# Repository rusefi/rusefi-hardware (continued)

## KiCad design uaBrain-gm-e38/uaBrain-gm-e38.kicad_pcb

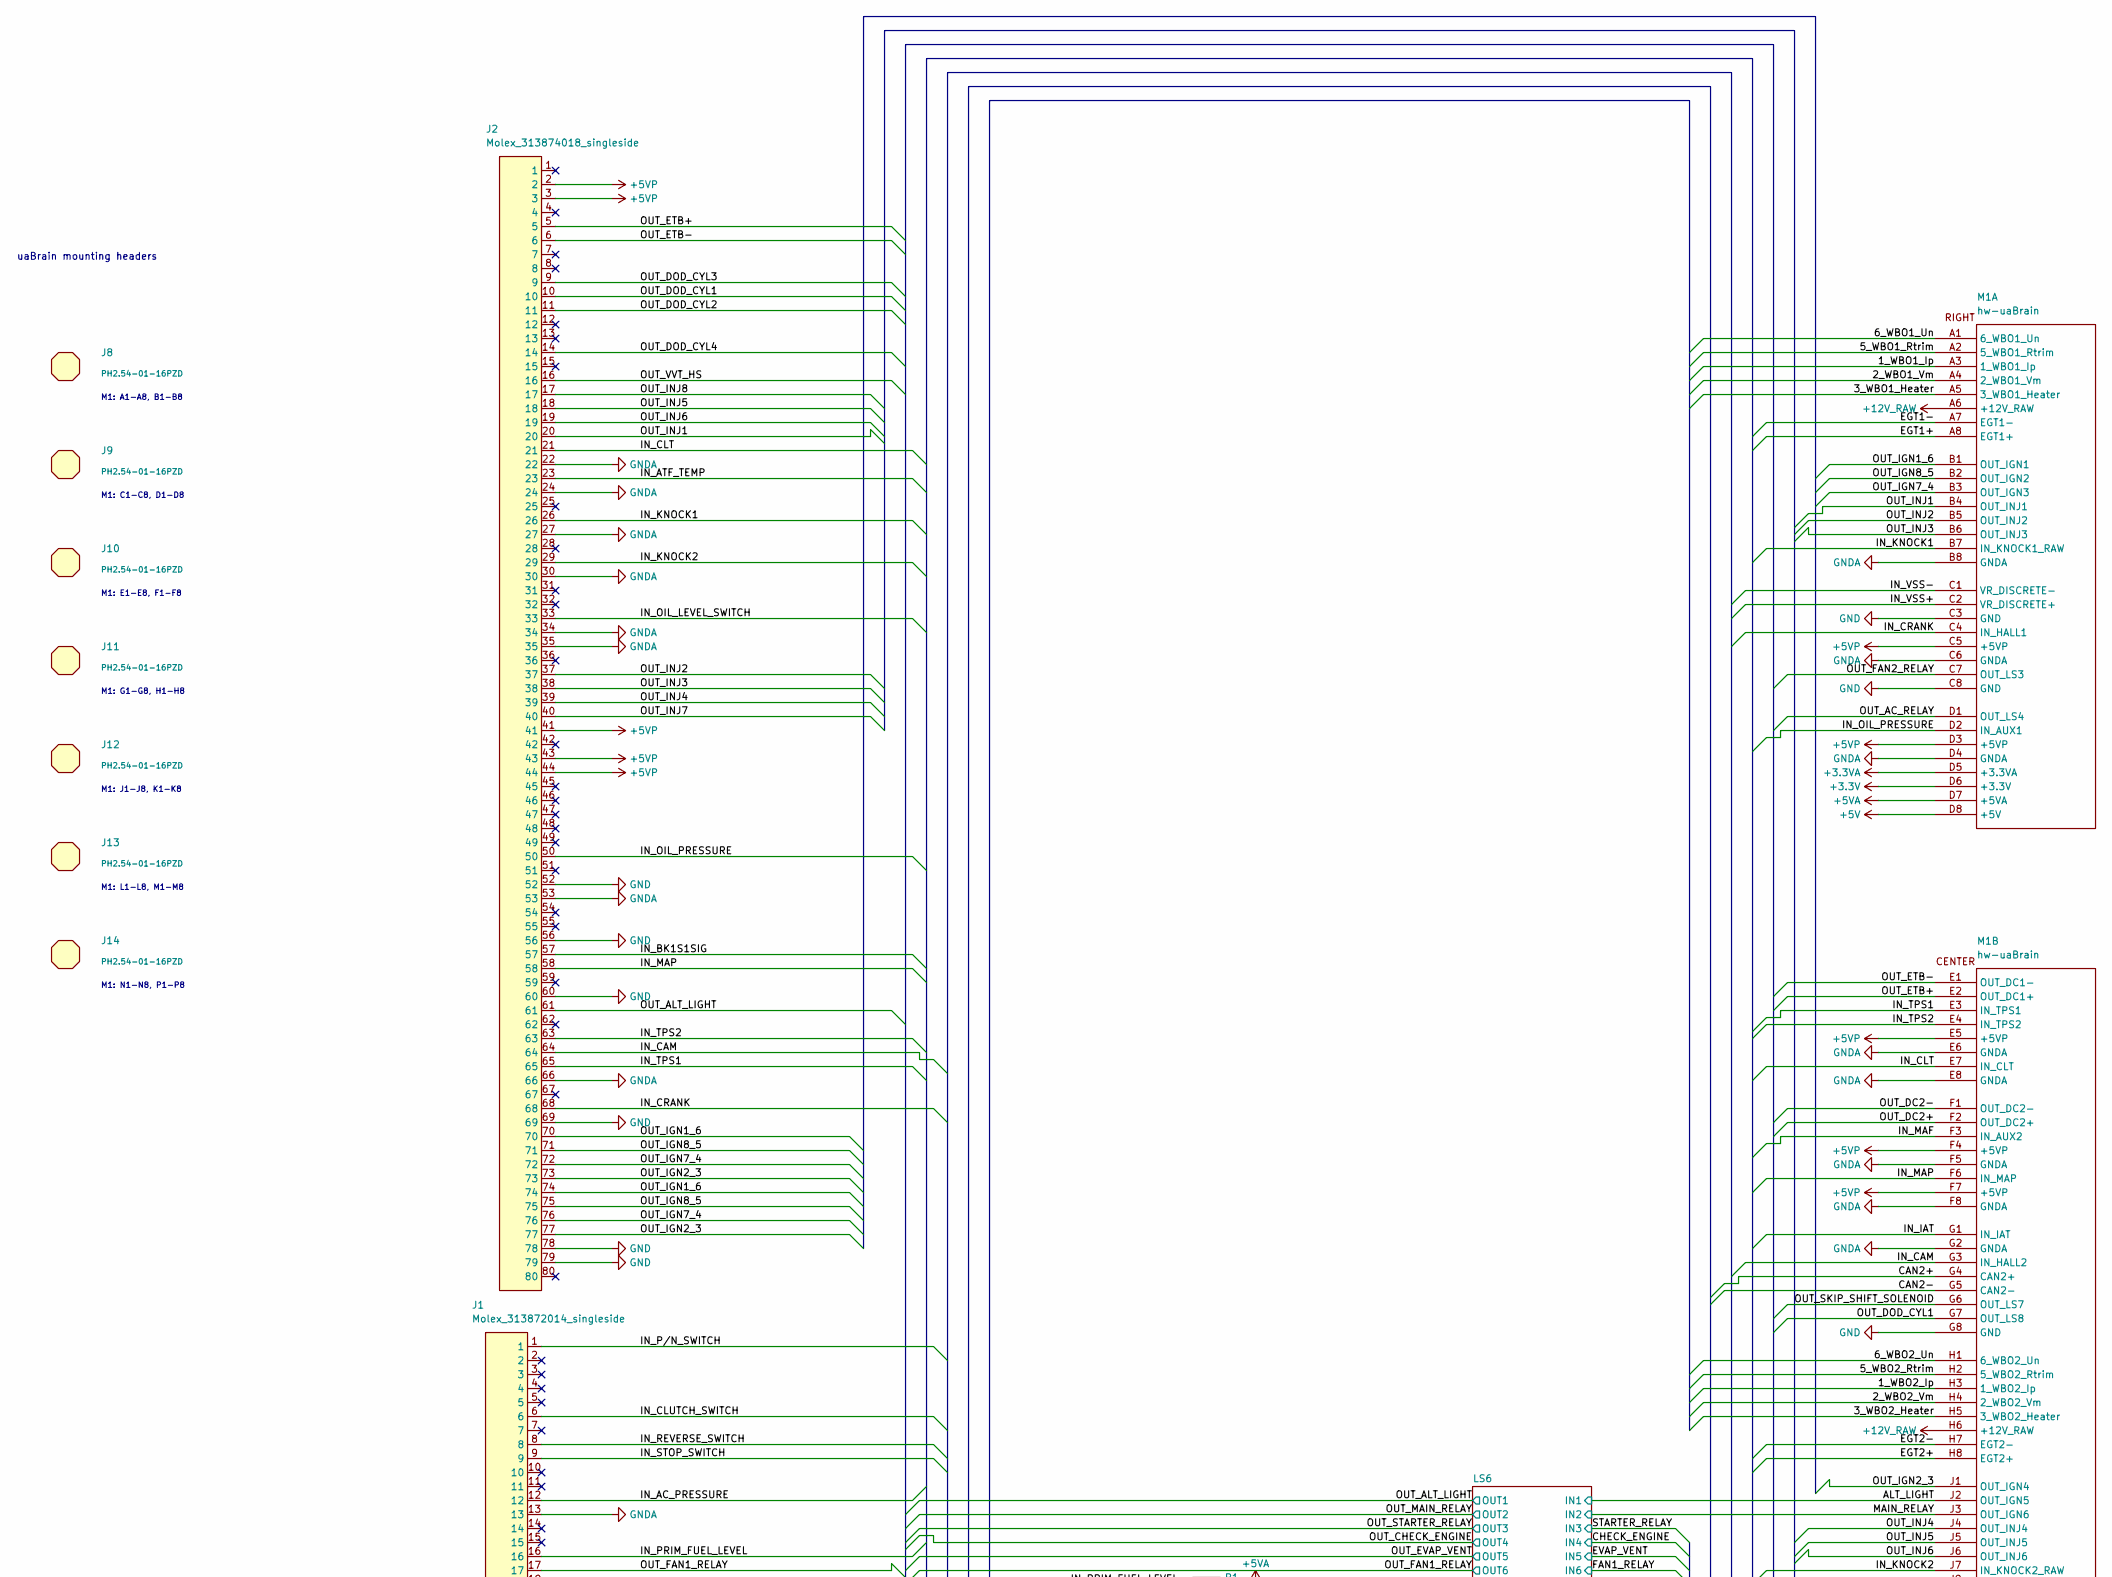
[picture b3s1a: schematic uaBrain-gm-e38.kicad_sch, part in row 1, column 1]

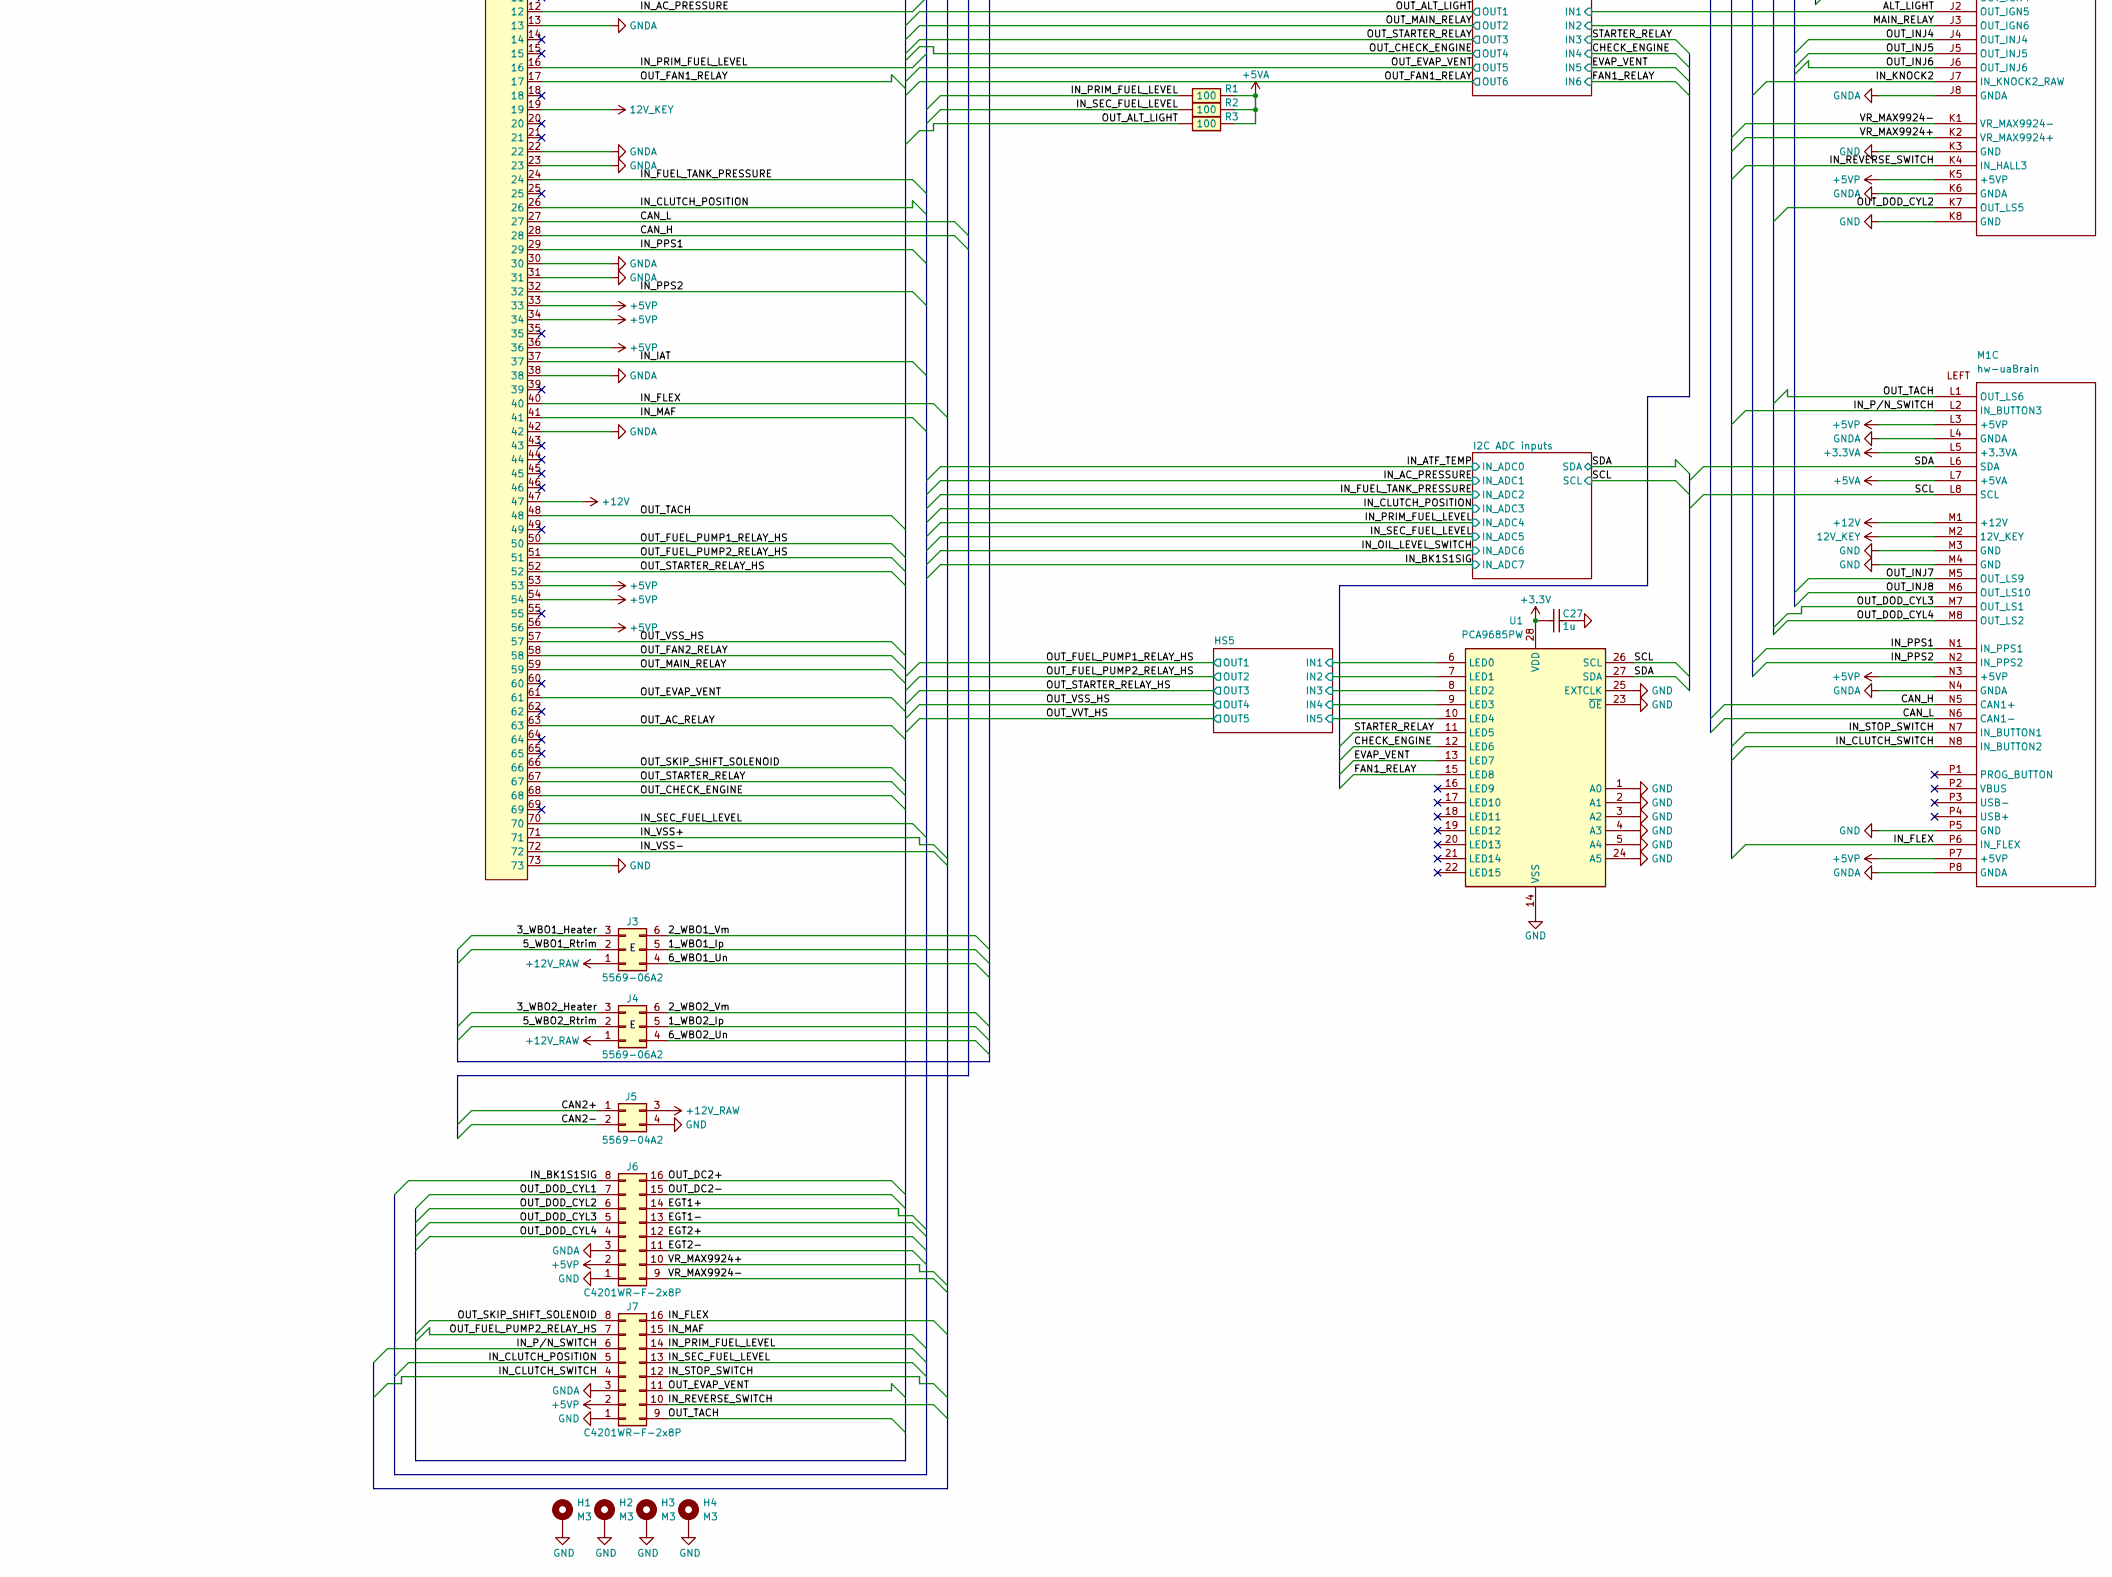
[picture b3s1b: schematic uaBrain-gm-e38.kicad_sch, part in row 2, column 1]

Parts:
C27: 1u; C0603; LCSC C15849
H1, H2, H3, H4: M3; MountingHole_3.2mm_M3_Pad_Via
J1: Molex_313872014_singleside; Molex_313872014_73pin_Connector
J2: Molex_313874018_singleside; Molex_313874018_80pin_Connector
J3, J4: 5569-06A2; Molex_Mini-Fit_Jr_5569-06A2_2x03_P4.20mm_Horizontal; LCSC C293509
J5: 5569-04A2; Molex_Mini-Fit_Jr_5569-04A2_2x02_P4.20mm_Horizontal; LCSC C234187
J6, J7: C4201WR-F-2x8P; Molex_Mini-Fit_Jr_5569-16A2_2x08_P4.20mm_Horizontal; LCSC C5355564
J8, J9, J10, J11, J12, J13, J14: PH2.54-01-16PZD; PinHeader_1x16_P2.54mm_Vertical; LCSC C7501590
M1: hw-uaBrain; hw-uaBrain-PinHeader
R1, R2, R3: 100; R_2512_6332Metric_Pad1.40x3.35mm_HandSolder; LCSC C24920
U1: PCA9685PW; TSSOP-28_4.4x9.7mm_P0.65mm; LCSC C2678753

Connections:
12V_KEY: J1.19, M1.M2 (12V_KEY)
+3.3V: C27.2, M1.D6 (+3.3V), U1.28 (VDD)
+3.3VA: M1.D5 (+3.3VA), M1.L5 (+3.3VA); also elsewhere on the board
+5V: M1.D8 (+5V)
+5VA: M1.D7 (+5VA), M1.L7 (+5VA), R1.1, R2.1, R3.1; also elsewhere on the board
+5VP: J1.33, J1.34, J1.36, J1.53, J1.54, J1.56, J2.2, J2.3, J2.41, J2.43, J2.44, J6.2, J7.2, M1.C5 (+5VP), M1.D3 (+5VP), M1.E5 (+5VP), M1.F4 (+5VP), M1.F7 (+5VP), M1.K5 (+5VP), M1.L3 (+5VP), M1.N3 (+5VP), M1.P7 (+5VP)
+12V: J1.47, M1.M1 (+12V)
+12V_RAW: J3.1, J4.1, J5.3, M1.A6 (+12V_RAW), M1.H6 (+12V_RAW); also elsewhere on the board
/1_WBO1_Ip: J3.5, M1.A3 (1_WBO1_Ip)
/1_WBO2_Ip: J4.5, M1.H3 (1_WBO2_Ip)
/2_WBO1_Vm: J3.6, M1.A4 (2_WBO1_Vm)
/2_WBO2_Vm: J4.6, M1.H4 (2_WBO2_Vm)
/3_WBO1_Heater: J3.3, M1.A5 (3_WBO1_Heater)
/3_WBO2_Heater: J4.3, M1.H5 (3_WBO2_Heater)
/5_WBO1_Rtrim: J3.2, M1.A2 (5_WBO1_Rtrim)
/5_WBO2_Rtrim: J4.2, M1.H2 (5_WBO2_Rtrim)
/6_WBO1_Un: J3.4, M1.A1 (6_WBO1_Un)
/6_WBO2_Un: J4.4, M1.H1 (6_WBO2_Un)
/ALT_LIGHT: M1.J2 (OUT_IGN5); also elsewhere on the board
/CAN2+: J5.1, M1.G4 (CAN2+)
/CAN2-: J5.2, M1.G5 (CAN2-)
/CAN_H: J1.28, M1.N5 (CAN1+)
/CAN_L: J1.27, M1.N6 (CAN1-)
/CHECK_ENGINE: U1.12 (LED6); also elsewhere on the board
/EGT1+: J6.14, M1.A8 (EGT1+)
/EGT1-: J6.13, M1.A7 (EGT1-)
/EGT2+: J6.12, M1.H8 (EGT2+)
/EGT2-: J6.11, M1.H7 (EGT2-)
/EVAP_VENT: U1.13 (LED7); also elsewhere on the board
/FAN1_RELAY: U1.15 (LED8); also elsewhere on the board
/HS5/IN1: U1.6 (LED0); also elsewhere on the board
/HS5/IN2: U1.7 (LED1); also elsewhere on the board
/HS5/IN3: U1.8 (LED2); also elsewhere on the board
/HS5/IN4: U1.9 (LED3); also elsewhere on the board
/HS5/IN5: U1.10 (LED4); also elsewhere on the board
/IN_AC_PRESSURE: J1.12; also elsewhere on the board
/IN_ATF_TEMP: J2.23; also elsewhere on the board
/IN_BK1S1SIG: J2.57, J6.8; also elsewhere on the board
/IN_CAM: J2.64, M1.G3 (IN_HALL2)
/IN_CLT: J2.21, M1.E7 (IN_CLT)
/IN_CLUTCH_POSITION: J1.26, J7.5; also elsewhere on the board
/IN_CLUTCH_SWITCH: J1.6, J7.4, M1.N8 (IN_BUTTON2)
/IN_CRANK: J2.68, M1.C4 (IN_HALL1)
/IN_FLEX: J1.40, J7.16, M1.P6 (IN_FLEX)
/IN_FUEL_TANK_PRESSURE: J1.24; also elsewhere on the board
/IN_IAT: J1.37, M1.G1 (IN_IAT)
/IN_KNOCK1: J2.26, M1.B7 (IN_KNOCK1_RAW)
/IN_KNOCK2: J2.29, M1.J7 (IN_KNOCK2_RAW)
/IN_MAF: J1.41, J7.15, M1.F3 (IN_AUX2)
/IN_MAP: J2.58, M1.F6 (IN_MAP)
/IN_OIL_LEVEL_SWITCH: J2.33; also elsewhere on the board
/IN_OIL_PRESSURE: J2.50, M1.D2 (IN_AUX1)
/IN_PPS1: J1.29, M1.N1 (IN_PPS1)
/IN_PPS2: J1.32, M1.N2 (IN_PPS2)
/IN_PRIM_FUEL_LEVEL: J1.16, J7.14, R1.2; also elsewhere on the board
/IN_P/N_SWITCH: J1.1, J7.6, M1.L2 (IN_BUTTON3)
/IN_REVERSE_SWITCH: J1.8, J7.10, M1.K4 (IN_HALL3)
/IN_SEC_FUEL_LEVEL: J1.70, J7.13, R2.2; also elsewhere on the board
/IN_STOP_SWITCH: J1.9, J7.12, M1.N7 (IN_BUTTON1)
/IN_TPS1: J2.65, M1.E3 (IN_TPS1)
/IN_TPS2: J2.63, M1.E4 (IN_TPS2)
/IN_VSS+: J1.71, M1.C2 (VR_DISCRETE+)
/IN_VSS-: J1.72, M1.C1 (VR_DISCRETE-)
/MAIN_RELAY: M1.J3 (OUT_IGN6); also elsewhere on the board
/OUT_AC_RELAY: J1.63, M1.D1 (OUT_LS4)
/OUT_ALT_LIGHT: J2.61, R3.2; also elsewhere on the board
/OUT_CHECK_ENGINE: J1.68; also elsewhere on the board
/OUT_DC2+: J6.16, M1.F2 (OUT_DC2+)
/OUT_DC2-: J6.15, M1.F1 (OUT_DC2-)
/OUT_DOD_CYL1: J2.10, J6.7, M1.G7 (OUT_LS8)
/OUT_DOD_CYL2: J2.11, J6.6, M1.K7 (OUT_LS5)
/OUT_DOD_CYL3: J2.9, J6.5, M1.M7 (OUT_LS1)
/OUT_DOD_CYL4: J2.14, J6.4, M1.M8 (OUT_LS2)
/OUT_ETB+: J2.5, M1.E2 (OUT_DC1+)
/OUT_ETB-: J2.6, M1.E1 (OUT_DC1-)
/OUT_EVAP_VENT: J1.61, J7.11; also elsewhere on the board
/OUT_FAN1_RELAY: J1.17; also elsewhere on the board
/OUT_FAN2_RELAY: J1.58, M1.C7 (OUT_LS3)
/OUT_FUEL_PUMP1_RELAY_HS: J1.50; also elsewhere on the board
/OUT_FUEL_PUMP2_RELAY_HS: J1.51, J7.7; also elsewhere on the board
/OUT_IGN1_6: J2.70, J2.74, M1.B1 (OUT_IGN1)
/OUT_IGN2_3: J2.73, J2.77, M1.J1 (OUT_IGN4)
/OUT_IGN7_4: J2.72, J2.76, M1.B3 (OUT_IGN3)
/OUT_IGN8_5: J2.71, J2.75, M1.B2 (OUT_IGN2)
/OUT_INJ1: J2.20, M1.B4 (OUT_INJ1)
/OUT_INJ2: J2.37, M1.B5 (OUT_INJ2)
/OUT_INJ3: J2.38, M1.B6 (OUT_INJ3)
/OUT_INJ4: J2.39, M1.J4 (OUT_INJ4)
/OUT_INJ5: J2.18, M1.J5 (OUT_INJ5)
/OUT_INJ6: J2.19, M1.J6 (OUT_INJ6)
/OUT_INJ7: J2.40, M1.M5 (OUT_LS9)
/OUT_INJ8: J2.17, M1.M6 (OUT_LS10)
/OUT_MAIN_RELAY: J1.59; also elsewhere on the board
/OUT_SKIP_SHIFT_SOLENOID: J1.66, J7.8, M1.G6 (OUT_LS7)
/OUT_STARTER_RELAY: J1.67; also elsewhere on the board
/OUT_STARTER_RELAY_HS: J1.52; also elsewhere on the board
/OUT_TACH: J1.48, J7.9, M1.L1 (OUT_LS6)
/OUT_VSS_HS: J1.57; also elsewhere on the board
/OUT_VVT_HS: J2.16; also elsewhere on the board
/SCL: M1.L8 (SCL), U1.26 (SCL); also elsewhere on the board
/SDA: M1.L6 (SDA), U1.27 (SDA); also elsewhere on the board
/STARTER_RELAY: U1.11 (LED5); also elsewhere on the board
/VR_MAX9924+: J6.10, M1.K2 (VR_MAX9924+)
/VR_MAX9924-: J6.9, M1.K1 (VR_MAX9924-)
GND: C27.1, H1.1 (1_1), H2.1 (1_1), H3.1 (1_1), H4.1 (1_1), J1.73, J2.52, J2.56, J2.60, J2.69, J2.78, J2.79, J5.4, J6.1, J7.1, M1.C3 (GND), M1.C8 (GND), M1.G8 (GND), M1.K3 (GND), M1.K8 (GND), M1.M3 (GND), M1.M4 (GND), M1.P5 (GND), U1.1 (A0), U1.2 (A1), U1.3 (A2), U1.4 (A3), U1.5 (A4), U1.14 (VSS), U1.23 (~OE), U1.24 (A5), U1.25 (EXTCLK); also elsewhere on the board
GNDA: J1.13, J1.22, J1.23, J1.30, J1.31, J1.38, J1.42, J2.22, J2.24, J2.27, J2.30, J2.34, J2.35, J2.53, J2.66, J6.3, J7.3, M1.B8 (GNDA), M1.C6 (GNDA), M1.D4 (GNDA), M1.E6 (GNDA), M1.E8 (GNDA), M1.F5 (GNDA), M1.F8 (GNDA), M1.G2 (GNDA), M1.J8 (GNDA), M1.K6 (GNDA), M1.L4 (GNDA), M1.N4 (GNDA), M1.P8 (GNDA); also elsewhere on the board

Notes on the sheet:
uaBrain mounting headers
M1: A1-A8, B1-B8
M1: C1-C8, D1-D8
M1: E1-E8, F1-F8
M1: G1-G8, H1-H8
M1: J1-J8, K1-K8
M1: L1-L8, M1-M8
M1: N1-N8, P1-P8

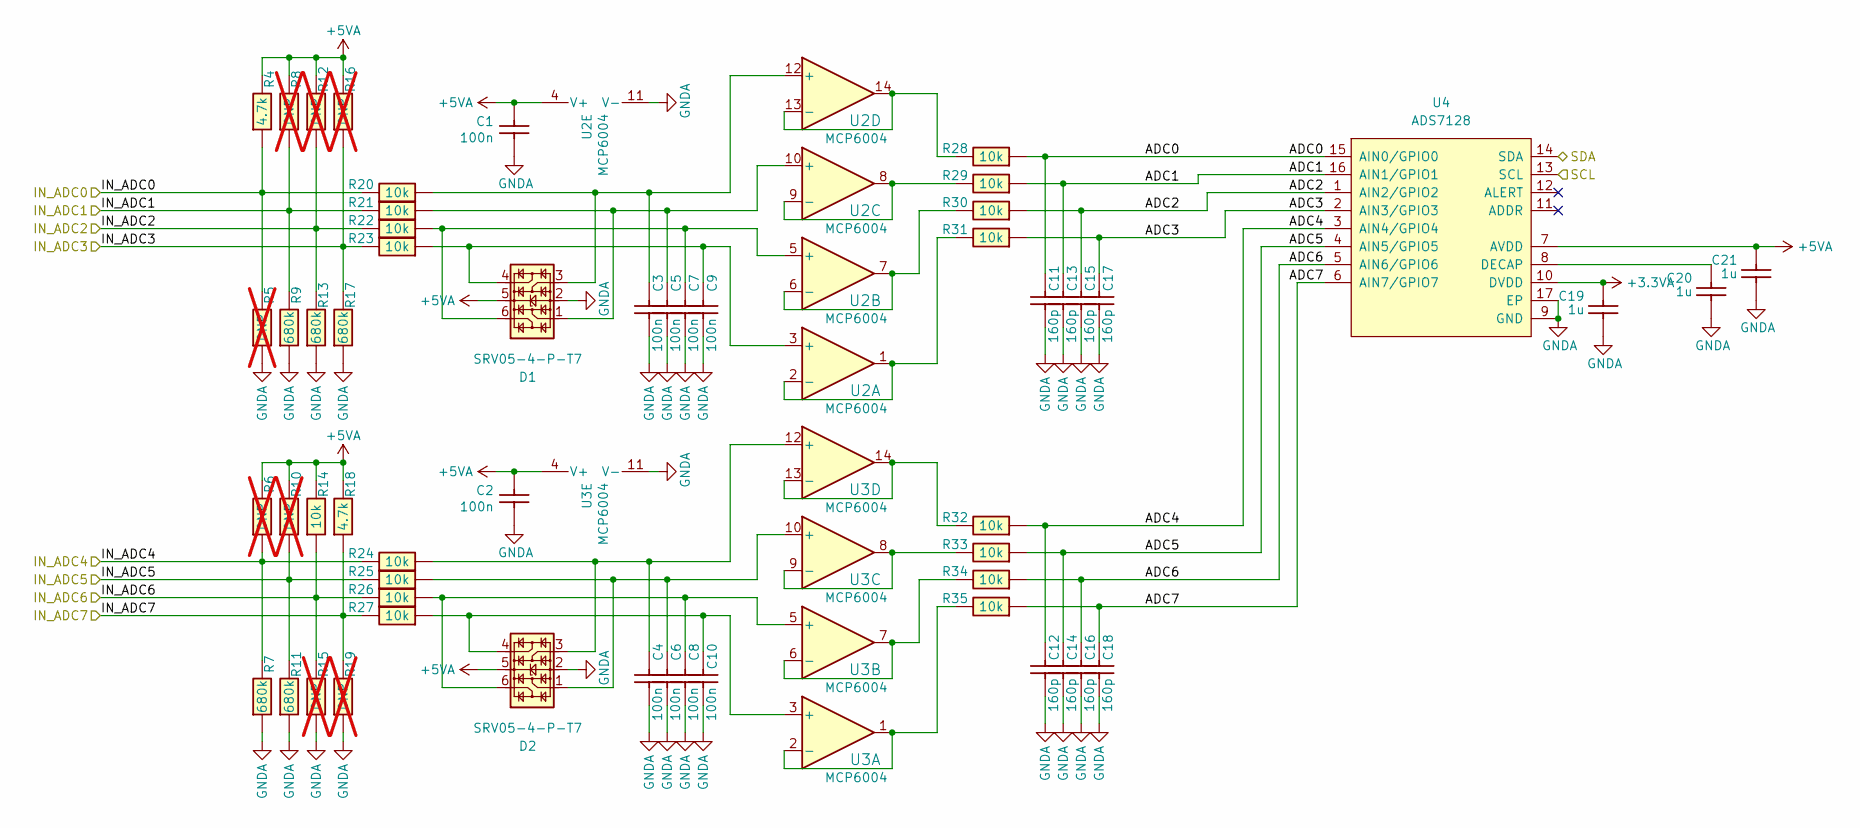
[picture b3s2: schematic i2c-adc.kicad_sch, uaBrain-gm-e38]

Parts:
C1, C2, C3, C4, C5, C6, C7, C8, C9, C10: 100n; C0603; LCSC C14663
C11, C12, C13, C14, C15, C16, C17, C18: 160p; C0603; LCSC C327274
C19, C20, C21: 1u; C0603; LCSC C15849
D1, D2: SRV05-4-P-T7; SOT-23-6; LCSC C6454456
R4, R18: 4.7k; R0603; LCSC C23162
R5, R6, R8, R10, R12, R15, R16, R19: DNP; R0603; not fitted
R7, R9, R11, R13, R17: 680k; R0603; LCSC C25822
R14, R20, R21, R22, R23, R24, R25, R26, R27, R28, R29, R30, R31, R32, R33, R34, R35: 10k; R0603; LCSC C15401
U2, U3: MCP6004; TSSOP-14_4.4x5mm_P0.65mm; Part # MCP6004T-I/ST; LCSC C50282
U4: ADS7128; WQFN-16-1EP_3x3mm_P0.5mm_EP1.68x1.68mm_ThermalVias; LCSC C2867992

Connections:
+3.3VA: C19.2, U4.10 (DVDD); also elsewhere on the board
+5VA: C1.2, C2.2, C21.2, D1.5, D2.5, R4.2, R6.2, R8.2, R10.2, R12.2, R14.2, R16.2, R18.2, U2.4 (V+), U3.4 (V+), U4.7 (AVDD); also elsewhere on the board
/I2C ADC inputs/ADC0: C11.2, R28.1, U4.15 (AIN0/GPIO0)
/I2C ADC inputs/ADC1: C13.2, R29.1, U4.16 (AIN1/GPIO1)
/I2C ADC inputs/ADC2: C15.2, R30.1, U4.1 (AIN2/GPIO2)
/I2C ADC inputs/ADC3: C17.2, R31.1, U4.2 (AIN3/GPIO3)
/I2C ADC inputs/ADC4: C12.2, R32.1, U4.3 (AIN4/GPIO4)
/I2C ADC inputs/ADC5: C14.2, R33.1, U4.4 (AIN5/GPIO5)
/I2C ADC inputs/ADC6: C16.2, R34.1, U4.5 (AIN6/GPIO6)
/I2C ADC inputs/ADC7: C18.2, R35.1, U4.6 (AIN7/GPIO7)
/IN_AC_PRESSURE: R8.1, R9.2, R21.2; also elsewhere on the board
/IN_ATF_TEMP: R4.1, R5.2, R20.2; also elsewhere on the board
/IN_BK1S1SIG: R18.1, R19.2, R27.2; also elsewhere on the board
/IN_CLUTCH_POSITION: R16.1, R17.2, R23.2; also elsewhere on the board
/IN_FUEL_TANK_PRESSURE: R12.1, R13.2, R22.2; also elsewhere on the board
/IN_OIL_LEVEL_SWITCH: R14.1, R15.2, R26.2; also elsewhere on the board
/IN_PRIM_FUEL_LEVEL: R6.1, R7.2, R24.2; also elsewhere on the board
/IN_SEC_FUEL_LEVEL: R10.1, R11.2, R25.2; also elsewhere on the board
/SCL: U4.13 (SCL); also elsewhere on the board
/SDA: U4.14 (SDA); also elsewhere on the board
GNDA: C1.1, C2.1, C3.1, C4.1, C5.1, C6.1, C7.1, C8.1, C9.1, C10.1, C11.1, C12.1, C13.1, C14.1, C15.1, C16.1, C17.1, C18.1, C19.1, C20.1, C21.1, D1.2, D2.2, R5.1, R7.1, R9.1, R11.1, R13.1, R15.1, R17.1, R19.1, U2.11 (V-), U3.11 (V-), U4.9 (GND), U4.17 (EP); also elsewhere on the board
unnamed: C9.2, D1.4, R23.1, U2.3 (+)
unnamed: R31.2, U2.1, U2.2 (-)
unnamed: C7.2, D1.6, R22.1, U2.5 (+)
unnamed: R30.2, U2.6 (-), U2.7
unnamed: C5.2, D1.1, R21.1, U2.10 (+)
unnamed: R29.2, U2.8, U2.9 (-)
unnamed: C3.2, D1.3, R20.1, U2.12 (+)
unnamed: R28.2, U2.13 (-), U2.14
unnamed: C10.2, D2.4, R27.1, U3.3 (+)
unnamed: R35.2, U3.1, U3.2 (-)
unnamed: C8.2, D2.6, R26.1, U3.5 (+)
unnamed: R34.2, U3.6 (-), U3.7
unnamed: C6.2, D2.1, R25.1, U3.10 (+)
unnamed: R33.2, U3.8, U3.9 (-)
unnamed: C4.2, D2.3, R24.1, U3.12 (+)
unnamed: R32.2, U3.13 (-), U3.14
unnamed: C20.2, U4.8 (DECAP)

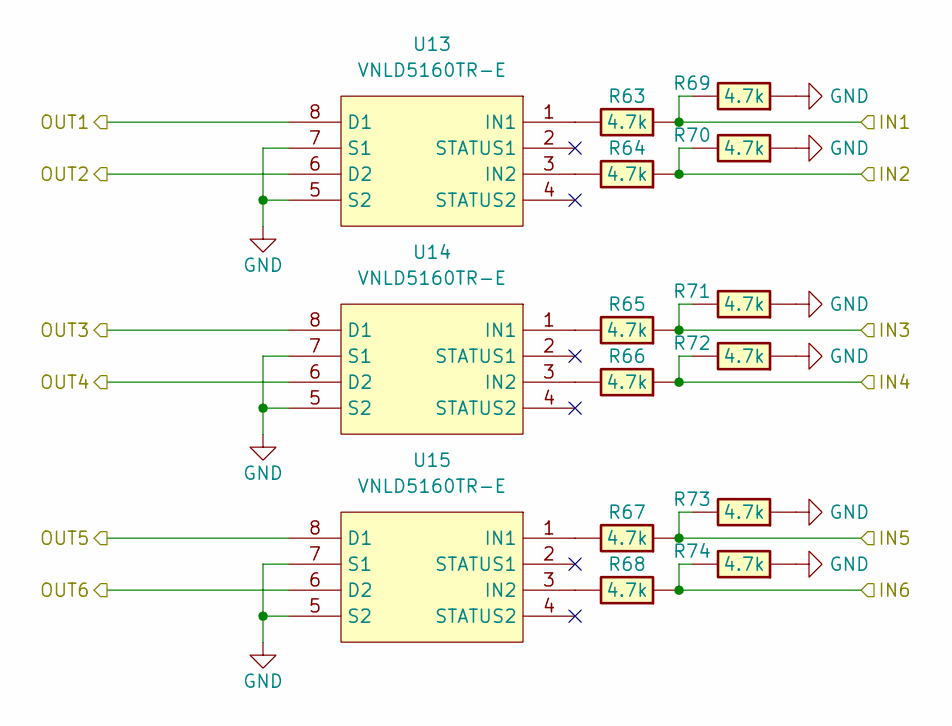
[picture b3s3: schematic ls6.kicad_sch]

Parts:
R63, R64, R65, R66, R67, R68, R69, R70, R71, R72, R73, R74: 4.7k; R0603; LCSC C23162
U13, U14, U15: VNLD5160TR-E; SOIC-8_3.9x4.9mm_P1.27mm; LCSC C377942

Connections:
/ALT_LIGHT: R63.1, R69.2; also elsewhere on the board
/CHECK_ENGINE: R66.1, R72.2; also elsewhere on the board
/EVAP_VENT: R67.1, R73.2; also elsewhere on the board
/FAN1_RELAY: R68.1, R74.2; also elsewhere on the board
/MAIN_RELAY: R64.1, R70.2; also elsewhere on the board
/OUT_ALT_LIGHT: U13.8 (D1); also elsewhere on the board
/OUT_CHECK_ENGINE: U14.6 (D2); also elsewhere on the board
/OUT_EVAP_VENT: U15.8 (D1); also elsewhere on the board
/OUT_FAN1_RELAY: U15.6 (D2); also elsewhere on the board
/OUT_MAIN_RELAY: U13.6 (D2); also elsewhere on the board
/OUT_STARTER_RELAY: U14.8 (D1); also elsewhere on the board
/STARTER_RELAY: R65.1, R71.2; also elsewhere on the board
GND: R69.1, R70.1, R71.1, R72.1, R73.1, R74.1, U13.5 (S2), U13.7 (S1), U14.5 (S2), U14.7 (S1), U15.5 (S2), U15.7 (S1); also elsewhere on the board
unnamed: R63.2, U13.1 (IN1)
unnamed: R64.2, U13.3 (IN2)
unnamed: R65.2, U14.1 (IN1)
unnamed: R66.2, U14.3 (IN2)
unnamed: R67.2, U15.1 (IN1)
unnamed: R68.2, U15.3 (IN2)

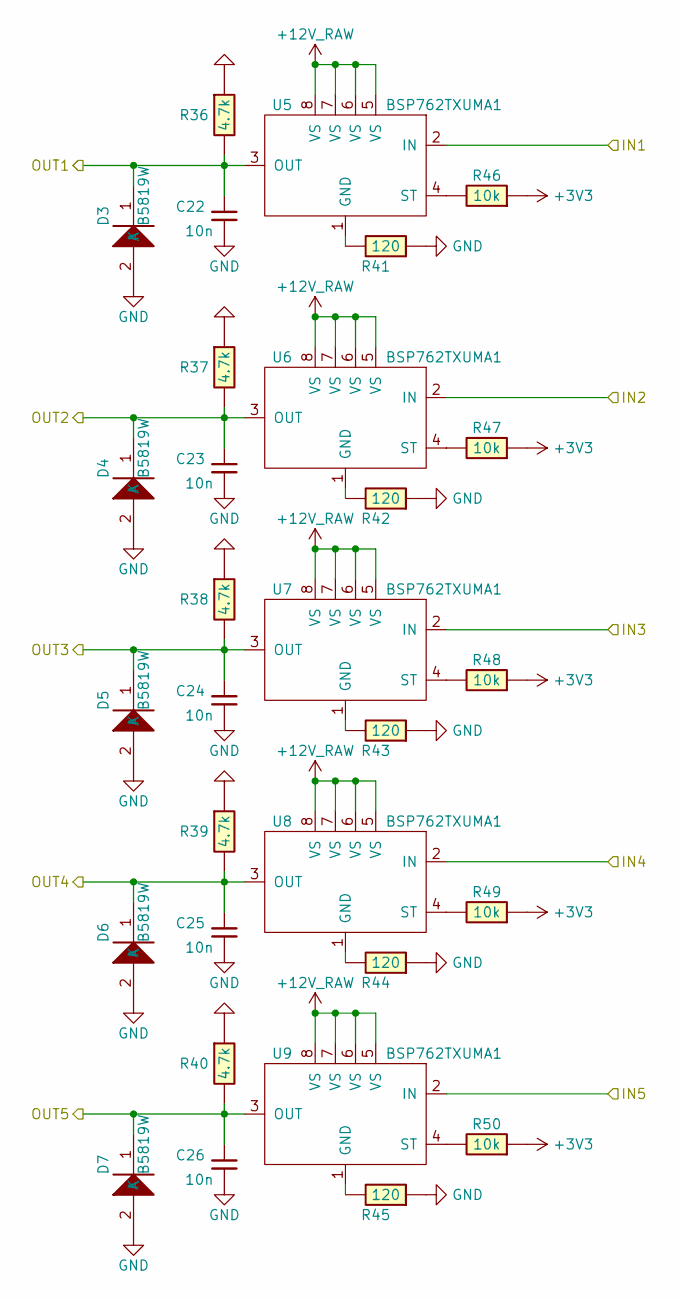
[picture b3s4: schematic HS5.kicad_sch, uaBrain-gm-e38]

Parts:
C22, C23, C24, C25, C26: 10n; C_0603_1608Metric; LCSC C57112
D3, D4, D5, D6, D7: B5819W; SOD-123; LCSC C8598
R36, R37, R38, R39, R40: 4.7k; R0603; LCSC C23162
R41, R42, R43, R44, R45: 120; R0603; LCSC C22787
R46, R47, R48, R49, R50: 10k; R0603; LCSC C25804
U5, U6, U7, U8, U9: BSP762TXUMA1; SOIC-8_3.9x4.9mm_P1.27mm; LCSC C2653781

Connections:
+3V3: R46.1, R47.1, R48.1, R49.1, R50.1
+12V_RAW: U5.5 (VS), U5.6 (VS), U5.7 (VS), U5.8 (VS), U6.5 (VS), U6.6 (VS), U6.7 (VS), U6.8 (VS), U7.5 (VS), U7.6 (VS), U7.7 (VS), U7.8 (VS), U8.5 (VS), U8.6 (VS), U8.7 (VS), U8.8 (VS), U9.5 (VS), U9.6 (VS), U9.7 (VS), U9.8 (VS); also elsewhere on the board
/HS5/IN1: U5.2 (IN); also elsewhere on the board
/HS5/IN2: U6.2 (IN); also elsewhere on the board
/HS5/IN3: U7.2 (IN); also elsewhere on the board
/HS5/IN4: U8.2 (IN); also elsewhere on the board
/HS5/IN5: U9.2 (IN); also elsewhere on the board
/OUT_FUEL_PUMP1_RELAY_HS: C22.1, D3.1 (K), R36.2, U5.3 (OUT); also elsewhere on the board
/OUT_FUEL_PUMP2_RELAY_HS: C23.1, D4.1 (K), R37.2, U6.3 (OUT); also elsewhere on the board
/OUT_STARTER_RELAY_HS: C24.1, D5.1 (K), R38.2, U7.3 (OUT); also elsewhere on the board
/OUT_VSS_HS: C25.1, D6.1 (K), R39.2, U8.3 (OUT); also elsewhere on the board
/OUT_VVT_HS: C26.1, D7.1 (K), R40.2, U9.3 (OUT); also elsewhere on the board
GND: C22.2, C23.2, C24.2, C25.2, C26.2, D3.2 (A), D4.2 (A), D5.2 (A), D6.2 (A), D7.2 (A), R36.1, R37.1, R38.1, R39.1, R40.1, R41.1, R42.1, R43.1, R44.1, R45.1; also elsewhere on the board
unnamed: R41.2, U5.1 (GND)
unnamed: R46.2, U5.4 (ST)
unnamed: R42.2, U6.1 (GND)
unnamed: R47.2, U6.4 (ST)
unnamed: R43.2, U7.1 (GND)
unnamed: R48.2, U7.4 (ST)
unnamed: R44.2, U8.1 (GND)
unnamed: R49.2, U8.4 (ST)
unnamed: R45.2, U9.1 (GND)
unnamed: R50.2, U9.4 (ST)

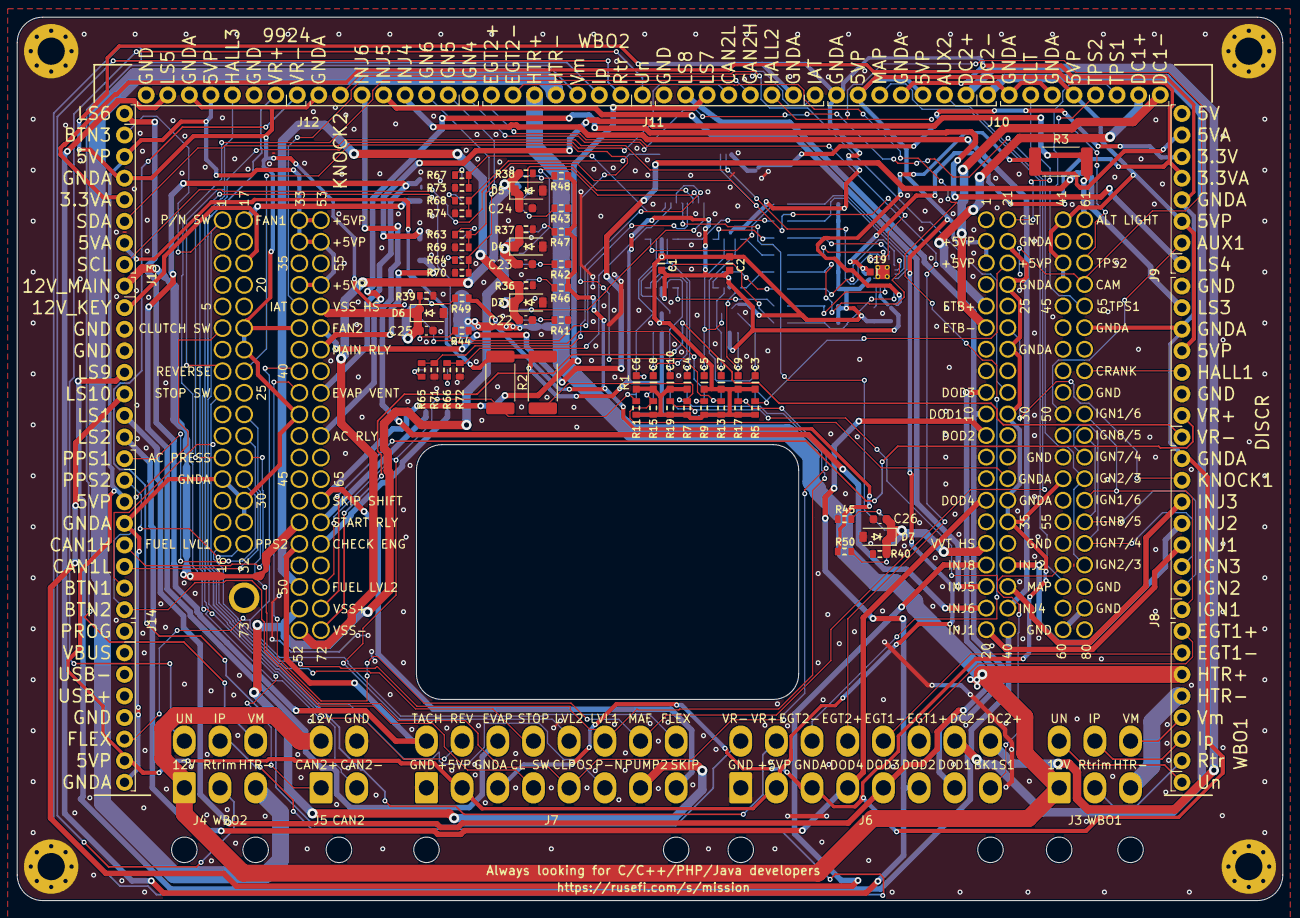
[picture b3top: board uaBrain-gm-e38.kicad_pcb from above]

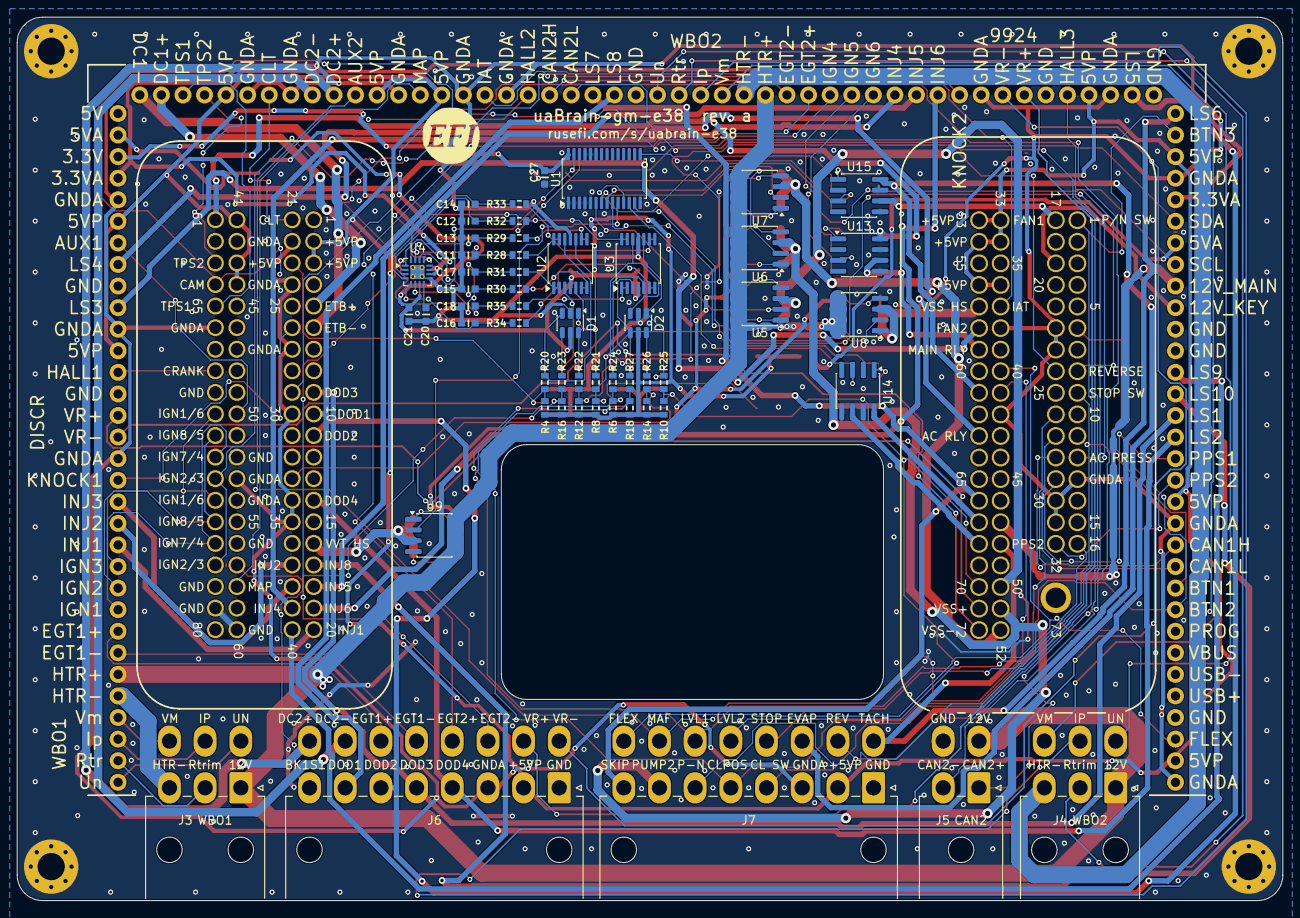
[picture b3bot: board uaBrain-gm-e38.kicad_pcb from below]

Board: 2 copper layers, 149.0 x 104.0 mm, 128 parts (57 on the bottom side), 147 nets.

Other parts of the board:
G1: RUSEFI_LOGO; rusefi_logo

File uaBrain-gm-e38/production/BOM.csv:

Comment,Designator,Footprint,LCSC Part #,Quantity
100n,"C1,C2,C3,C4,C5,C6,C7,C8,C9,C10",hellen-one-common:C0603,C14663,10
160p,"C11,C12,C13,C14,C15,C16,C17,C18",hellen-one-common:C0603,C327274,8
1u,"C19,C20,C21,C27",hellen-one-common:C0603,C15849,4
10n,"C22,C23,C24,C25,C26",Capacitor_SMD:C_0603_1608Metric,C57112,5
SRV05-4-P-T7,"D1,D2",Package_TO_SOT_SMD:SOT-23-6,C6454456,2
B5819W,"D3,D4,D5,D6,D7",hellen-one-common:SOD-123,C8598,5
Molex_313872014_singleside,J1,kicad6-libraries:Molex_313872014_73pin_Connector,,1
Molex_313874018_singleside,J2,kicad6-libraries:Molex_313874018_80pin_Connector,,1
5569-06A2,"J3,J4",Connector_Molex:Molex_Mini-Fit_Jr_5569-06A2_2x03_P4.20mm_Horizontal,C293509,2
5569-04A2,J5,Connector_Molex:Molex_Mini-Fit_Jr_5569-04A2_2x02_P4.20mm_Horizontal,C234187,1
C4201WR-F-2x8P,"J6,J7",Connector_Molex:Molex_Mini-Fit_Jr_5569-16A2_2x08_P4.20mm_Horizontal,C5355564,2
PH2.54-01-16PZD,"J8,J9,J10,J11,J12,J13,J14",Connector_PinHeader_2.54mm:PinHeader_1x16_P2.54mm_Vertical,C7501590,7
100,"R1,R2,R3",Resistor_SMD:R_2512_6332Metric_Pad1.40x3.35mm_HandSolder,C24920,3
4.7k,"R4,R18,R36,R37,R38,R39,R40,R63,R64,R65,R66,R67,R68,R69,R70,R71,R72,R73,R74",hellen-one-common:R0603,C23162,19
680k,"R7,R9,R11,R13,R17",hellen-one-common:R0603,C25822,5
10k,"R14,R20,R21,R22,R23,R24,R25,R26,R27,R28,R29,R30,R31,R32,R33,R34,R35",hellen-one-common:R0603,C15401,17
120,"R41,R42,R43,R44,R45",hellen-one-common:R0603,C22787,5
10k,"R46,R47,R48,R49,R50",hellen-one-common:R0603,C25804,5
PCA9685PW,U1,Package_SO:TSSOP-28_4.4x9.7mm_P0.65mm,C2678753,1
MCP6004,"U2,U3",Package_SO:TSSOP-14_4.4x5mm_P0.65mm,C50282,2
ADS7128,U4,Package_DFN_QFN:WQFN-16-1EP_3x3mm_P0.5mm_EP1.68x1.68mm_ThermalVias,C2867992,1
BSP762TXUMA1,"U5,U6,U7,U8,U9",Package_SO:SOIC-8_3.9x4.9mm_P1.27mm,C2653781,5
VNLD5160TR-E,"U13,U14,U15",Package_SO:SOIC-8_3.9x4.9mm_P1.27mm,C377942,3
